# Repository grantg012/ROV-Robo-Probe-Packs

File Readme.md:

# Readme for ROV - Robo Probe Packs

This PCB serves as a integration layer for basic ROVs (though it could be
creatively used in other applications). It is designed for modularity and
fitting multiple different configurations. Perfect for high schoolers with
a little electronics experience, but not PCB design.

Features include:
* Pins for connecting to an Arduino Uno or Mega (use double sides ones for best effect)
* 12V+ input with reverse voltage protection
* Connections to common 12V -> 5V converters (such as ...)
* Up to 6 Electronic Speed Controllers (with options for protection circuitry)
* Breakouts for servos and I2C
* Primarily through hole components for easy soldering

## See `versions` for schematic PDFs and gerber files

## Parts List
* Arduino Uno or Mega
* Anderson power pole to PCB (1377G12 or similar)

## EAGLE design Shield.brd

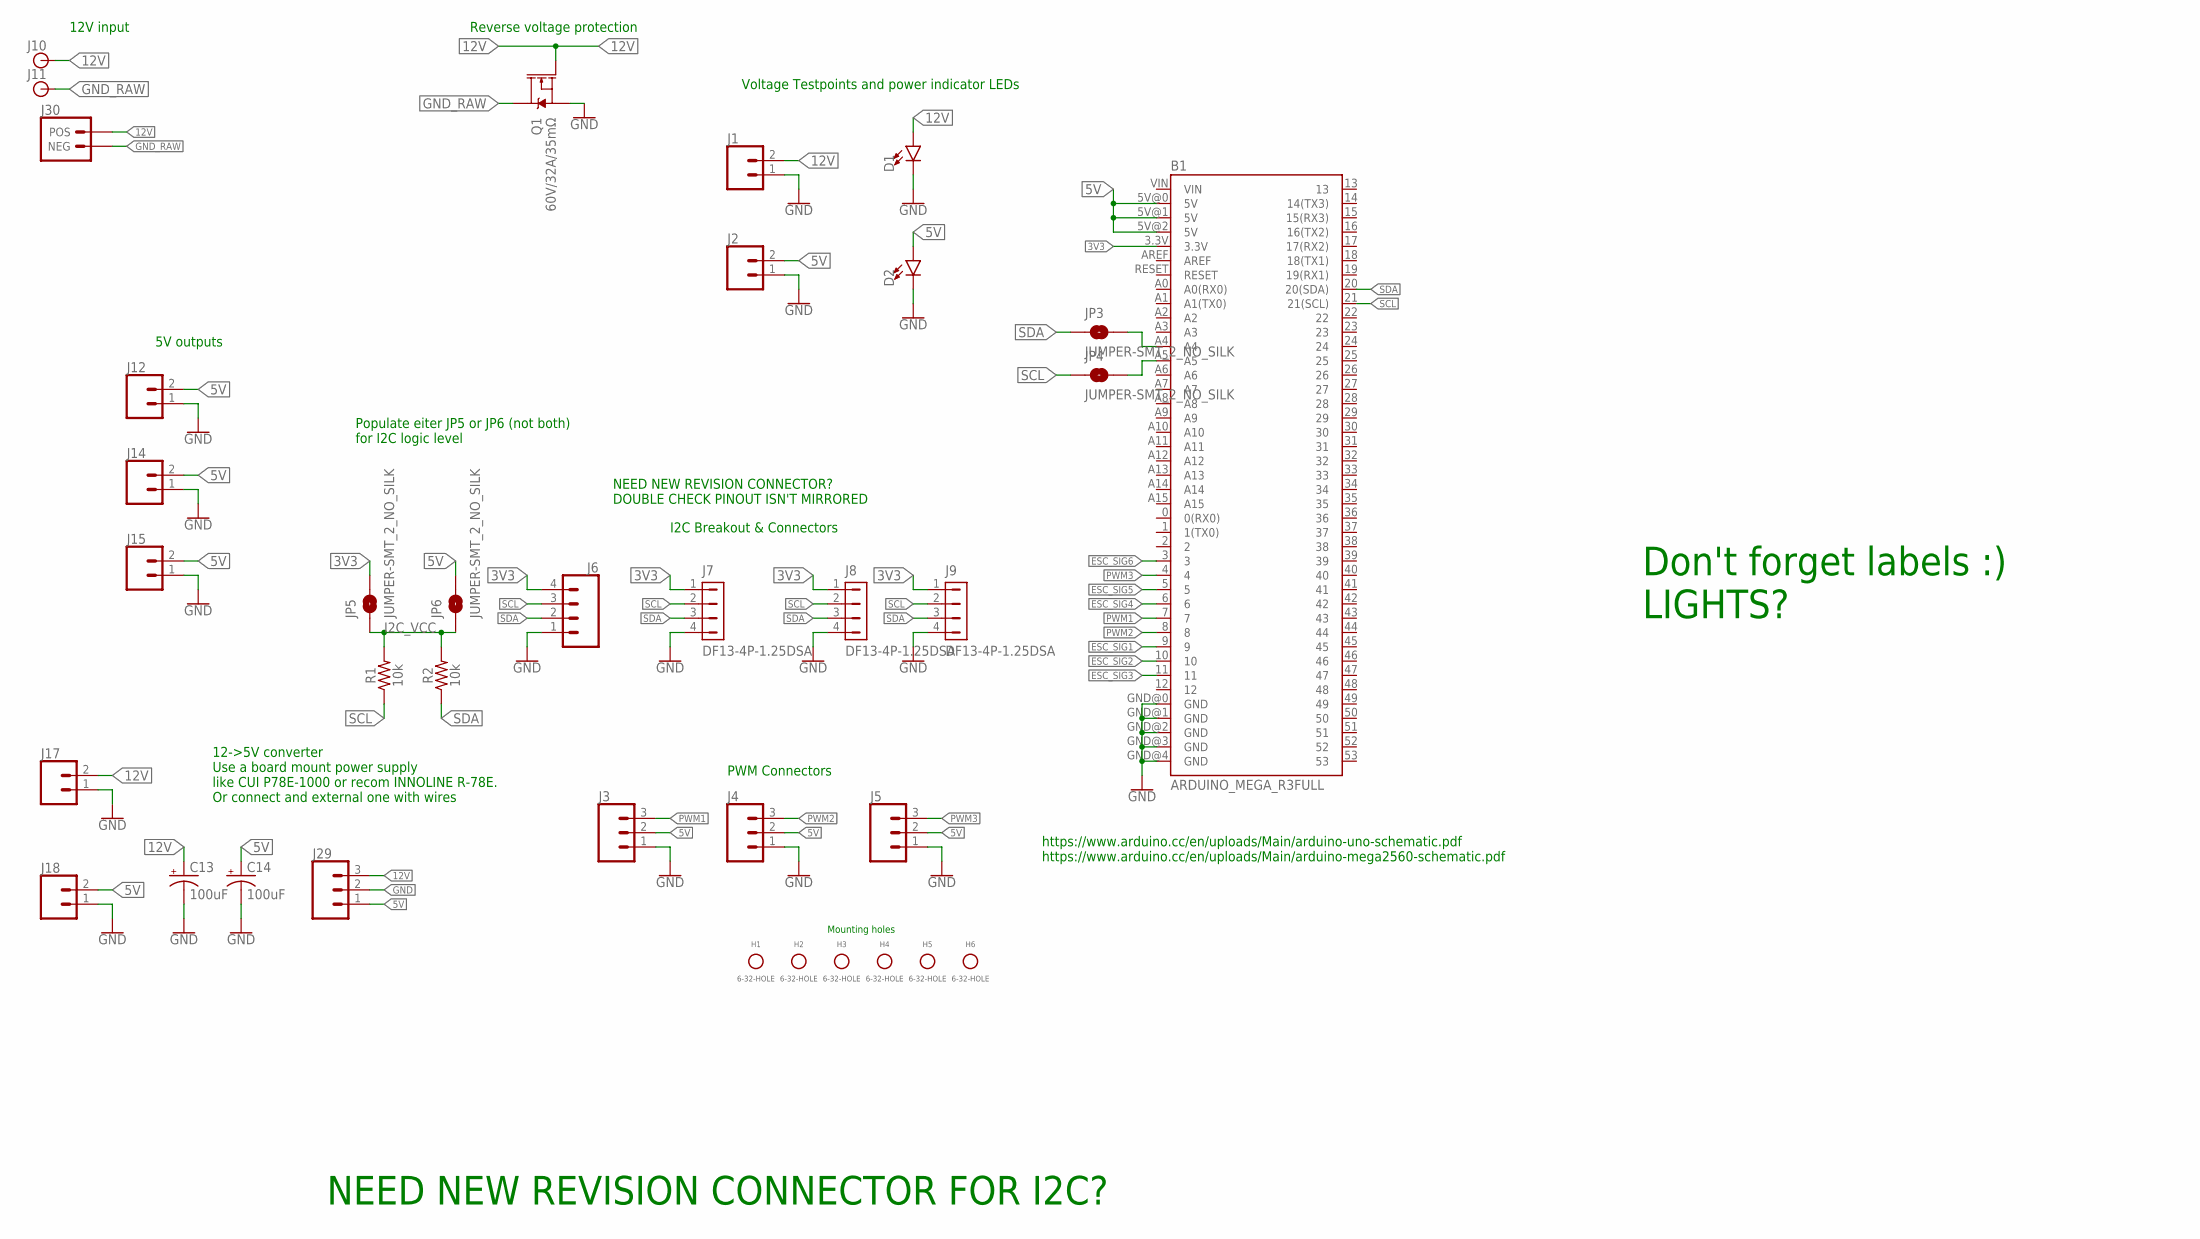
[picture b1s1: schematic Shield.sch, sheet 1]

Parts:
B1: ARDUINO_MEGA_R3FULL; ARDUINO_MEGA
C13, C14: 100uF; CPOL-RADIAL-2.5MM-6.5MM
D1, D2: LED3MM; LED_3MM
H1, H2, H3, H4, H5, H6: 6-32-HOLE
J1, J2, J12, J14, J15, J17, J18: CONN_02; 1X02
J3, J4, J5, J29: CONN_03; 1X03
J6: CONN_04; 1X04
J7, J8, J9: DF13-4P-1.25DSA
J10, J11: BANANA_PTH; BANANA_CONN_NO_THERM
J30: ANDERON_POWERPOLE_2
JP3, JP4, JP5, JP6: JUMPER-SMT_2_NO_SILK; SMT-JUMPER_2_NO_SILK
Q1: 60V/32A/35mΩ; TO220V
R1, R2: 10k; AXIAL-0.3

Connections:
3V3: B1.3.3V, J6.4, J7.1, J8.1, J9.1, JP5.2
5V: B1.5V@0 (5V), B1.5V@1 (5V), B1.5V@2 (5V), C14.1 (+), D2.A, J2.2, J3.2, J4.2, J5.2, J12.2, J14.2, J15.2, J18.2, J29.1, JP6.2
12V: C13.1 (+), D1.A, J1.2, J10.1, J17.2, J29.3, J30.POS, Q1.1 (G); also elsewhere on the board
A4_SDA: B1.A4, JP3.2
A5_SCL: B1.A5, JP4.2
ESC_SIG1: B1.9; also elsewhere on the board
ESC_SIG2: B1.10; also elsewhere on the board
ESC_SIG3: B1.11; also elsewhere on the board
ESC_SIG4: B1.6; also elsewhere on the board
ESC_SIG5: B1.5; also elsewhere on the board
ESC_SIG6: B1.3; also elsewhere on the board
GND: B1.GND@0 (GND), B1.GND@1 (GND), B1.GND@2 (GND), B1.GND@3 (GND), B1.GND@4 (GND), C13.2 (-), C14.2 (-), D1.K (C), D2.K (C), J1.1, J2.1, J3.1, J4.1, J5.1, J6.1, J7.4, J8.4, J9.4, J12.1, J14.1, J15.1, J17.1, J18.1, J29.2, Q1.3 (S); also elsewhere on the board
GND_RAW: J11.1, J30.NEG, Q1.2 (D)
I2C_VCC: JP5.1, JP6.1, R1.P$2 (2), R2.P$2 (2)
PWM1: B1.7, J3.3
PWM2: B1.8, J4.3
PWM3: B1.4, J5.3
SCL: B1.21 (21(SCL)), J6.3, J7.2, J8.2, J9.2, JP4.1, R1.P$1 (1)
SDA: B1.20 (20(SDA)), J6.2, J7.3, J8.3, J9.3, JP3.1, R2.P$1 (1)

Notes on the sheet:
12V input
12->5V converter Use a board mount power supply like CUI P78E-1000 or recom INNOLINE R-78E. Or connect and external one with wires
5V outputs
https://www.arduino.cc/en/uploads/Main/arduino-uno-schematic.pdf https://www.arduino.cc/en/uploads/Main/arduino-mega2560-schematic.pdf
Reverse voltage protection
Voltage Testpoints and power indicator LEDs
Don't forget labels :) LIGHTS?
I2C Breakout & Connectors
PWM Connectors
Mounting holes
Populate eiter JP5 or JP6 (not both) for I2C logic level
NEED NEW REVISION CONNECTOR? DOUBLE CHECK PINOUT ISN'T MIRRORED
NEED NEW REVISION CONNECTOR FOR I2C?

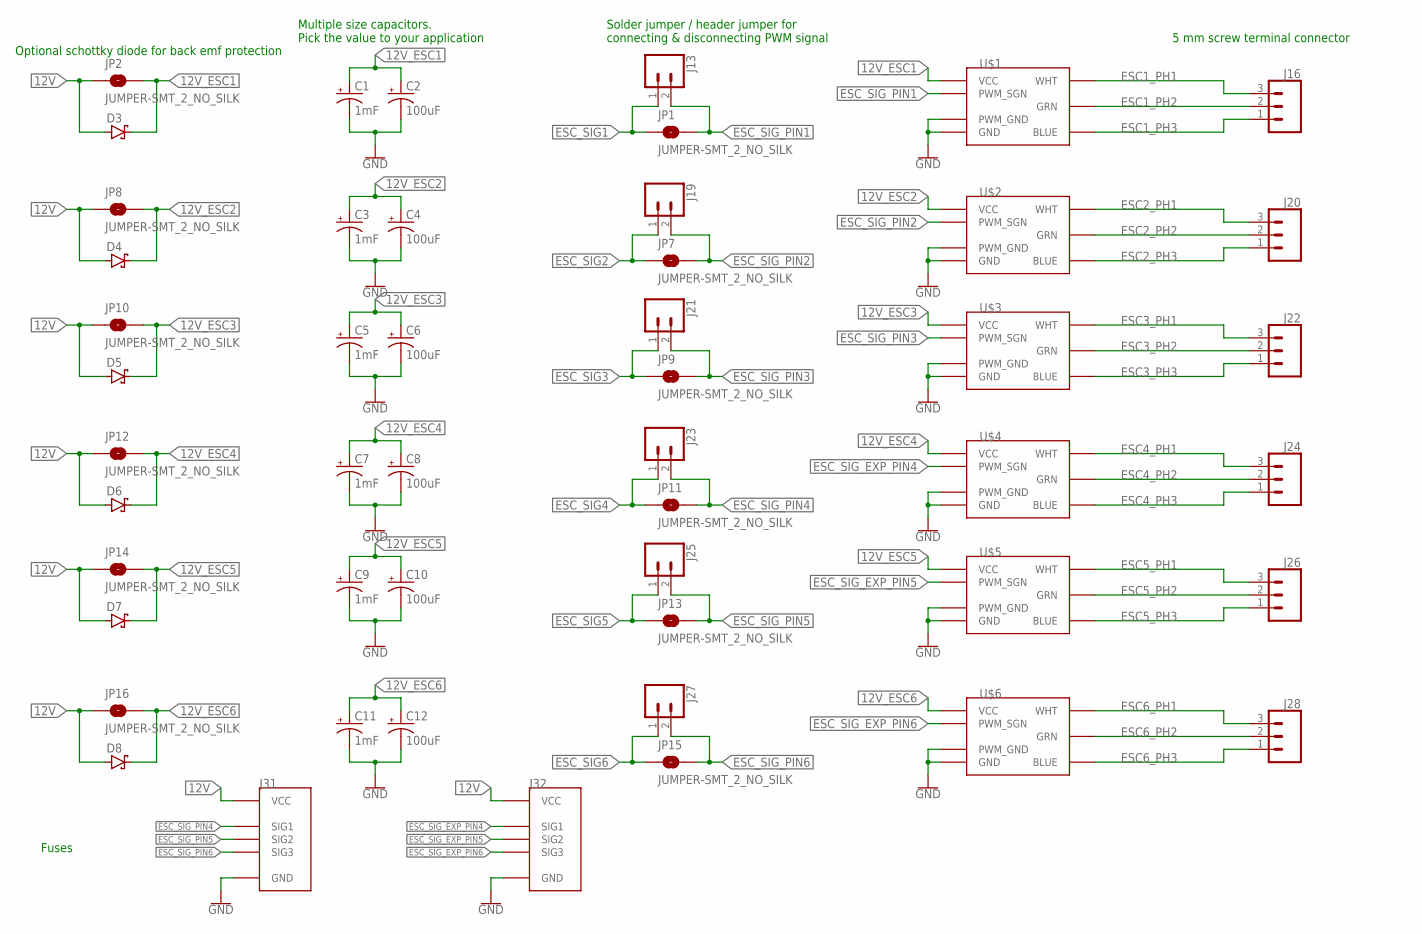
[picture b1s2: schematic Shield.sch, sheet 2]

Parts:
C1, C3, C5, C7, C9, C11: 1mF; CPOL-RADIAL-5MM-10MM
C2, C4, C6, C8, C10, C12: 100uF; CPOL-RADIAL-2.5MM-6.5MM
D3, D4, D5, D6, D7, D8: SCHOTTKY-DIODECB429-15; CB429-15
J13, J19, J21, J23, J25, J27: CONN_02; 1X02
J16, J20, J22, J24, J26, J28: CONN_03-SCREW-5MM; SCREWTERMINAL-5MM-3
J31, J32: ESC_EXPANSION_CONNECTOR; EXPANSION
JP1, JP2, JP7, JP8, JP9, JP10, JP11, JP12, JP13, JP14, JP15, JP16: JUMPER-SMT_2_NO_SILK; SMT-JUMPER_2_NO_SILK
U$1, U$2, U$3, U$4, U$5, U$6: ESC

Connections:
12V: D3.A, D4.A, D5.A, D6.A, D7.A, D8.A, J31.15 (VCC), J31.16 (VCC), J31.17 (VCC), J31.18 (VCC), J31.19 (VCC), J31.20 (VCC), J31.21 (VCC), J31.22 (VCC), J31.23 (VCC), J31.24 (VCC), J32.15 (VCC), J32.16 (VCC), J32.17 (VCC), J32.18 (VCC), J32.19 (VCC), J32.20 (VCC), J32.21 (VCC), J32.22 (VCC), J32.23 (VCC), J32.24 (VCC), JP2.1, JP8.1, JP10.1, JP12.1, JP14.1, JP16.1; also elsewhere on the board
12V_ESC1: C1.+, C2.1 (+), D3.C, JP2.2, U$1.VCC
12V_ESC2: C3.+, C4.1 (+), D4.C, JP8.2, U$2.VCC
12V_ESC3: C5.+, C6.1 (+), D5.C, JP10.2, U$3.VCC
12V_ESC4: C7.+, C8.1 (+), D6.C, JP12.2, U$4.VCC
12V_ESC5: C9.+, C10.1 (+), D7.C, JP14.2, U$5.VCC
12V_ESC6: C11.+, C12.1 (+), D8.C, JP16.2, U$6.VCC
ESC1_PH1: J16.3, U$1.BLUE (WHT)
ESC1_PH2: J16.2, U$1.GRN
ESC1_PH3: J16.1, U$1.WHT (BLUE)
ESC2_PH1: J20.3, U$2.BLUE (WHT)
ESC2_PH2: J20.2, U$2.GRN
ESC2_PH3: J20.1, U$2.WHT (BLUE)
ESC3_PH1: J22.3, U$3.BLUE (WHT)
ESC3_PH2: J22.2, U$3.GRN
ESC3_PH3: J22.1, U$3.WHT (BLUE)
ESC4_PH1: J24.3, U$4.BLUE (WHT)
ESC4_PH2: J24.2, U$4.GRN
ESC4_PH3: J24.1, U$4.WHT (BLUE)
ESC5_PH1: J26.3, U$5.BLUE (WHT)
ESC5_PH2: J26.2, U$5.GRN
ESC5_PH3: J26.1, U$5.WHT (BLUE)
ESC6_PH1: J28.3, U$6.BLUE (WHT)
ESC6_PH2: J28.2, U$6.GRN
ESC6_PH3: J28.1, U$6.WHT (BLUE)
ESC_SIG1: J13.1, JP1.1; also elsewhere on the board
ESC_SIG2: J19.1, JP7.1; also elsewhere on the board
ESC_SIG3: J21.1, JP9.1; also elsewhere on the board
ESC_SIG4: J23.1, JP11.1; also elsewhere on the board
ESC_SIG5: J25.1, JP13.1; also elsewhere on the board
ESC_SIG6: J27.1, JP15.1; also elsewhere on the board
ESC_SIG_EXP_PIN4: J32.11 (SIG1), U$4.PWM_SGN
ESC_SIG_EXP_PIN5: J32.12 (SIG2), U$5.PWM_SGN
ESC_SIG_EXP_PIN6: J32.13 (SIG3), U$6.PWM_SGN
ESC_SIG_PIN1: J13.2, JP1.2, U$1.PWM_SGN
ESC_SIG_PIN2: J19.2, JP7.2, U$2.PWM_SGN
ESC_SIG_PIN3: J21.2, JP9.2, U$3.PWM_SGN
ESC_SIG_PIN4: J23.2, J31.11 (SIG1), JP11.2
ESC_SIG_PIN5: J25.2, J31.12 (SIG2), JP13.2
ESC_SIG_PIN6: J27.2, J31.13 (SIG3), JP15.2
GND: C1.-, C2.2 (-), C3.-, C4.2 (-), C5.-, C6.2 (-), C7.-, C8.2 (-), C9.-, C10.2 (-), C11.-, C12.2 (-), J31.1 (GND), J31.2 (GND), J31.3 (GND), J31.4 (GND), J31.5 (GND), J31.6 (GND), J31.7 (GND), J31.8 (GND), J31.9 (GND), J31.10 (GND), J32.1 (GND), J32.2 (GND), J32.3 (GND), J32.4 (GND), J32.5 (GND), J32.6 (GND), J32.7 (GND), J32.8 (GND), J32.9 (GND), J32.10 (GND), U$1.GND, U$1.PWM_GND, U$2.GND, U$2.PWM_GND, U$3.GND, U$3.PWM_GND, U$4.GND, U$4.PWM_GND, U$5.GND, U$5.PWM_GND, U$6.GND, U$6.PWM_GND; also elsewhere on the board

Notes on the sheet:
Fuses
Solder jumper / header jumper for connecting & disconnecting PWM signal
Multiple size capacitors. Pick the value to your application
Optional schottky diode for back emf protection
5 mm screw terminal connector

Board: 2 copper layers, 86 parts (1 on the bottom side), 52 nets, no tracks yet.

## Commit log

2022-04-21 Added license
2022-04-21 More to do listing
2022-04-23 Split into two sheets and add most existing parts
2022-04-24 Finish all parts except fuses
2022-04-24 Switch to GPL License
2022-04-30 Add caps around buck converter (fixes #1)
2022-05-08 Size ESC for 0.1" gnd & sig headers. Add and use expansion.
2022-05-08 Begin board placement

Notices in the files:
parts and their libraries:
SparkFun-Boards: Licensing: Creative Commons ShareAlike 4.0 International - https://creativecommons.org/licenses/by-sa/4.0
